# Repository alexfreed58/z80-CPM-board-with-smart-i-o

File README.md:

# z80-CPM-board-with-smart-I/O
<p>This is yet another retro computer running CPM on an actual Z80 CPU with a twist. Instead of using a traditional UART for communications, it uses a RPi pico module that is no bigger and no more expensive than a UART. But it can do a whole lot more. On this board it also generates the CPU clock that can be set to any desired frequency. If you have a 20 MHz Z80, use 20 MHz.</p>
<p>
There is also a provision to add an ESP32 module that allows connecting to the board via WiFi (telnet server) or BlueTooth. Of course you need to load a simple program onto the ESP32 from the ESP32 examples with some  modifications. Arduino works well.</p>
<p>
I use an SD card for disk emulation. I made a lot of design choices to be somewhat compatible with John Winans' z80-retro computer: "disk" geometry and memory management in particular. However my SD interface is quite different. Instead of bit-banging SPI, I use a couple of TTL (or CMOS) chips. The heart of the interface is a 74(LS/HC)299 universal shift register and some glue logic. I have decided to use several off-the-shelf chips rather than  a single CPLD because if anybody decides to use my design, it will be a lot easier if you don't have much experience with programmable logic. As a result the SPI interface runs at the full CPU clock speed  and to transmit and receive a byte via SPI you only need to write one byte to an i/o port and read a byte back.</p> 
<p>
The board design is done with the (fantastic!) open source Kicad. Likely much less than perfect as it is my first Licad project ever. I used mostly Altium Designer for professional work, but since Kicad is free, anyone can modify and improve the board.</p>

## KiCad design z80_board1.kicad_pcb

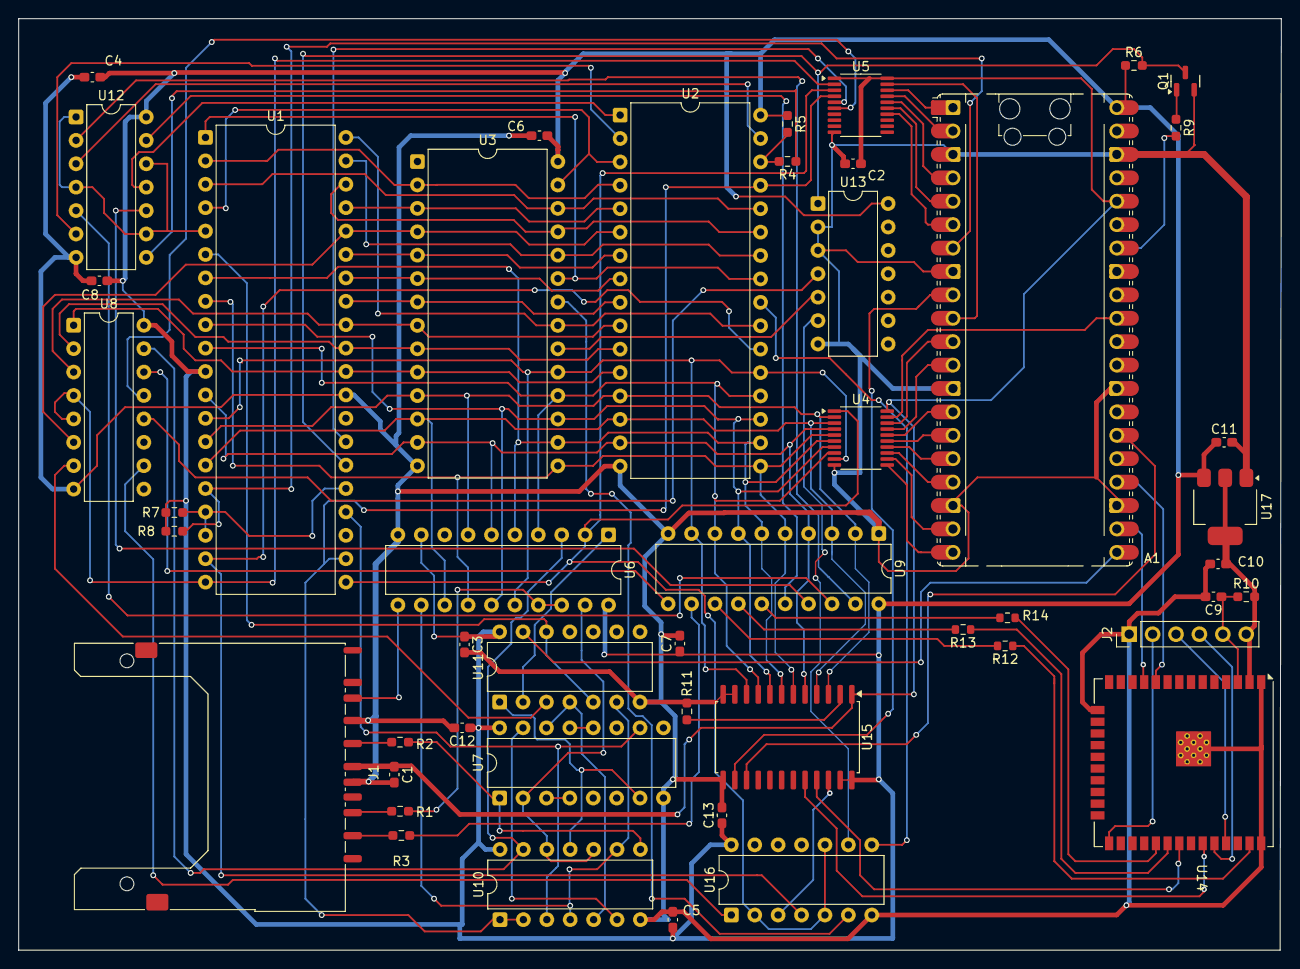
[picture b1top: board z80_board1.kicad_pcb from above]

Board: 2 copper layers, 137.0 x 101.1 mm, 48 parts (0 on the bottom side), 108 nets.

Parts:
A1: RaspberryPi_Pico; RaspberryPi_Pico_Common_Unspecified
C1, C2, C9, C10, C11: 0.1; C_0603_1608Metric_Pad1.08x0.95mm_HandSolder
C3, C4, C5, C6, C7, C8, C12, C13: C; C_0603_1608Metric_Pad1.08x0.95mm_HandSolder
J1: SD_Card_Receptacle; SD_Kyocera_145638009511859+
J2: Conn_01x06_Pin; PinHeader_1x06_P2.54mm_Vertical
Q1: MMBT2222A; SOT-23
R1, R2, R3, R4, R5, R6, R7, R8, R9, R11: 1K; R_0603_1608Metric_Pad0.98x0.95mm_HandSolder
R10: 10K; R_0603_1608Metric_Pad0.98x0.95mm_HandSolder
R12, R13: 1K; R_0603_1608Metric
R14: 1k; R_0603_1608Metric
U1: Z84C00xxP; DIP-40_W15.24mm
U2: AS6C4008; DIP-32_W15.24mm
U3: 27C256; DIP-28_W15.24mm
U4, U5: SN74LVC245APW; TSSOP-20_4.4x6.5mm_P0.65mm
U6: 74LS299; DIP-20_W7.62mm
U7: 74LS390; DIP-16_W7.62mm
U8: 74HC138; DIP-16_W7.62mm
U9: 74HCT574; DIP-20_W7.62mm
U10: 74LS27; DIP-14_W7.62mm
U11: 74HC04; DIP-14_W7.62mm
U12, U16: 74LS32; DIP-14_W7.62mm
U13: 74LS74; DIP-14_W7.62mm
U14: ESP32-WROOM-32UE
U15: SN74LVC8T245; SOIC-24W_7.5x15.4mm_P1.27mm
U17: AP1117-33; SOT-223-3_TabPin2

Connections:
+3.3V: A1.36 (3V3), C1.1, C2.1, J1.4 (VDD), U4.20 (VCC), U5.1 (DIR), U5.20 (VCC), U15.1 (V_{CCA})
/A3: U1.33 (A_{3}), U2.9 (A3), U3.7 (A3)
/A4: U1.34 (A_{4}), U2.8 (A4), U3.6 (A4)
/A5: U1.35 (A_{5}), U2.7 (A5), U3.5 (A5)
/A6: U1.36 (A_{6}), U2.6 (A6), U3.4 (A6), U8.6 (E2)
/A7: U1.37 (A_{7}), U2.5 (A7), U3.3 (A7)
/A8: U1.38 (A_{8}), U2.27 (A8), U3.25 (A8)
/A9: U1.39 (A_{9}), U2.26 (A9), U3.24 (A9)
/A10: U1.40 (A_{10}), U2.23 (A10), U3.21 (A10)
/A11: U1.1 (A_{11}), U2.25 (A11), U3.23 (A11)
/A12: U1.2 (A_{12}), U2.4 (A12), U3.2 (A12)
/A13: U1.3 (A_{13}), U2.28 (A13), U3.26 (A13)
/A14: U1.4 (A_{14}), U2.3 (A14), U3.27 (A14)
/A15: U1.5 (A_{15}), U12.1, U12.4, U12.9, U12.12
/ESP32_MISO: U14.31 (IO19), U15.21 (B1)
/Flag_pico: A1.9 (GPIO6), U15.14 (B8)
/RAM_OE: U2.24 (OE#), U16.8
/R_D0: A1.11 (GPIO8), U4.18 (B1)
/R_D1: A1.12 (GPIO9), U4.17 (B2)
/R_D2: A1.14 (GPIO10), U4.16 (B3)
/R_D3: A1.15 (GPIO11), U4.15 (B4)
/R_D4: A1.16 (GPIO12), U4.14 (B5)
/R_D5: A1.17 (GPIO13), U4.13 (B6)
/R_D6: A1.19 (GPIO14), U4.12 (B7)
/R_D7: A1.20 (GPIO15), U4.11 (B8)
/SD_interface/MISO: J1.7 (DAT0), U6.11 (Ds0)
/SD_interface/start_SD: U6.19 (S1), U7.2 (MR), U10.10, U10.12
/SD_interface//CS: J1.1 (CD/DAT3), R3.1
/busy: A1.26 (GPIO20), U15.15 (B7)
/io17: A1.24 (GPIO18), U14.10 (IO25)
/io18: A1.22 (GPIO17), U14.11 (IO26)
/sel_pico: U5.6 (A5), U8.13 (~Y2)
//oe_data: A1.31 (GPIO26_ADC0), U4.19 (~OE)
/~int: A1.7 (GPIO5), R8.2, U1.16 (~INT)
A0: U1.30 (A_{0}), U2.12 (A0), U3.10 (A0), U8.1 (A0)
A1: U1.31 (A_{1}), U2.11 (A1), U3.9 (A1), U8.2 (A1)
A2: U1.32 (A_{2}), U2.10 (A2), U3.8 (A2), U8.3 (A2)
CLK: U6.12 (Cp), U10.4, U10.9, U11.6
D0: U1.14 (D_{0}), U2.13 (DQ0), U3.11 (D0), U4.2 (A1), U6.7 (IO0), U9.2 (D0), U15.3 (A1)
D1: U1.15 (D_{1}), U2.14 (DQ1), U3.12 (D1), U4.3 (A2), U6.13 (IO1), U9.3 (D1), U15.4 (A2)
D2: U1.12 (D_{2}), U2.15 (DQ2), U3.13 (D2), U4.4 (A3), U6.6 (IO2), U9.4 (D2), U15.5 (A3)
D3: U1.8 (D_{3}), U2.17 (DQ3), U3.15 (D3), U4.5 (A4), U6.14 (IO3), U9.5 (D3), U15.6 (A4)
D4: U1.7 (D_{4}), U2.18 (DQ4), U3.16 (D4), U4.6 (A5), U6.5 (IO4), U9.6 (D4), U15.7 (A5)
D5: U1.9 (D_{5}), U2.19 (DQ5), U3.17 (D5), U4.7 (A6), U6.15 (IO5), U9.7 (D5), U15.8 (A6)
D6: U1.10 (D_{6}), U2.20 (DQ6), U3.18 (D6), U4.8 (A7), U6.4 (IO6), U9.8 (D6), U15.9 (A7)
D7: U1.13 (D_{7}), U2.21 (DQ7), U3.19 (D7), U4.9 (A8), U6.16 (IO7), U9.9 (D7), U15.10 (A8)
GND: A1.3 (GND), A1.8 (GND), A1.13 (GND), A1.18 (GND), A1.23 (GND), A1.28 (GND), A1.38 (GND), C1.2, C2.2, C3.2, C4.2, C5.2, C6.2, C7.2, C8.2, C9.2, C10.2, C11.2, C12.2, C13.2, J1.3 (VSS), J1.6 (VSS), J2.1, Q1.2 (E), R11.1, U1.29 (GND), U2.16 (VSS), U3.1 (VPP), U3.14 (GND), U4.10 (GND), U5.10 (GND), U6.10 (GND), U7.8 (GND), U8.8 (GND), U9.1 (OE), U9.10 (GND), U10.7 (GND), U11.7 (GND), U12.7 (GND), U13.2 (D), U13.3 (C), U13.7 (GND), U14.1 (GND), U14.15 (GND), U14.38 (GND), U14.39 (GND), U15.11 (GND), U15.12 (GND), U15.13 (GND), U16.7 (GND), U17.1 (GND)
unnamed: A1.1 (GPIO0), U5.18 (B1)
unnamed: A1.2 (GPIO1), U5.17 (B2)
unnamed: A1.4 (GPIO2), U5.16 (B3)
unnamed: A1.5 (GPIO3), U5.15 (B4)
unnamed: A1.6 (GPIO4), U5.14 (B5)
unnamed: A1.10 (GPIO7), U5.19 (~OE)
unnamed: A1.21 (GPIO16), U11.13
unnamed: A1.34 (GPIO28_ADC2), R9.2
unnamed: J1.5 (CLK), R2.2
unnamed: J1.2 (CMD), R1.2
unnamed: J2.2, U14.25 (IO0)
unnamed: J2.3, U14.35 (TXD0/IO1)
unnamed: J2.4, U14.34 (RXD0/IO3)
unnamed: C9.1, J2.5, R10.1, U14.3 (EN)
unnamed: C10.1, J2.6, R10.2, U14.2 (VDD), U17.2 (VO)
unnamed: Q1.1 (B), R9.1
unnamed: R4.1, U12.8
unnamed: U1.6 (CLK), U11.5, U11.12
unnamed: R7.2, U1.17 (~NMI), U1.18 (~HALT), U1.25 (~BUSREQ)
unnamed: U1.27 (~M1), U5.5 (A4)
unnamed: U2.31 (A15), U12.3
unnamed: U2.2 (A16), U12.6
unnamed: R4.2, R5.2, U2.30 (A17)
unnamed: U2.1 (A18), U12.11
unnamed: U3.22 (~OE), U16.6
unnamed: R1.1, U6.17 (Q7), U6.18 (Ds7)
unnamed: U6.1 (S0), U11.2
unnamed: U7.3 (Q0), U7.4 (~CP1)
unnamed: U7.7 (Q3), U10.11, U11.1
unnamed: R2.1, U7.1 (~CP0), U10.8
unnamed: U7.14 (MR), U10.5, U11.4
unnamed: U7.12 (~CP1), U7.13 (Q0)
unnamed: U7.15 (~CP0), U10.6
unnamed: U8.10 (~Y5), U16.1
unnamed: R3.2, U9.12 (Q7)
unnamed: U3.20 (~CE), U13.5 (Q)
unnamed: U13.6 (~Q), U16.9
unnamed: U8.12 (~Y3), U13.4 (~S)
unnamed: R14.1, U14.29 (IO5)
unnamed: R13.1, U14.30 (IO18)
unnamed: R12.1, U14.37 (IO23)
unnamed: R11.2, U15.2 (DIR)
unnamed: U15.22 (~OE), U16.3
U9_Q4: R14.2, U9.15 (Q4)
U9_Q5: R13.2, U9.14 (Q5)
U9_Q6: R12.2, U9.13 (Q6)
VCC: A1.40 (VBUS), C3.1, C4.1, C5.1, C6.1, C7.1, C8.1, C11.1, C12.1, C13.1, R5.1, R6.1, R7.1, R8.1, U1.11 (V_{CC}), U2.32 (VCC), U3.28 (VCC), U6.9 (Mr), U6.20 (VCC), U7.16 (VCC), U8.16 (VCC), U9.20 (VCC), U10.14 (VCC), U11.14 (VCC), U12.14 (VCC), U13.14 (VCC), U15.23 (V_{CCB}), U15.24 (V_{CCB}), U16.14 (VCC), U17.3 (VI)
attn: U14.33 (IO21), U15.20 (B2)
bank_a15: U9.19 (Q0), U12.2
bank_a16: U9.18 (Q1), U12.5
bank_a17: U9.17 (Q2), U12.10
bank_a18: U9.16 (Q3), U12.13
sel_IO: U8.14 (~Y1), U9.11 (Cp)
sel_SD: U6.3 (OE2), U8.15 (~Y0), U10.13
sel_wait: U8.7 (~Y7), U11.3
wait: U1.24 (~WAIT), U7.10 (Q2), U10.3
/MREQ: U1.19 (~MREQ), U2.22 (CE#), U16.4
/RST: Q1.3 (C), R6.2, U1.26 (~RESET), U13.1 (~R)
/iorq: U1.20 (~IORQ), U5.2 (A1), U8.4 (~E0), U8.5 (~E1)
/rd: U1.21 (~RD), U4.1 (DIR), U5.3 (A2), U6.2 (OE1), U16.2, U16.5, U16.10
/wr: U1.22 (~WR), U2.29 (WE#), U5.4 (A3), U10.1, U10.2

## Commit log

2026-06-23 added PDF
